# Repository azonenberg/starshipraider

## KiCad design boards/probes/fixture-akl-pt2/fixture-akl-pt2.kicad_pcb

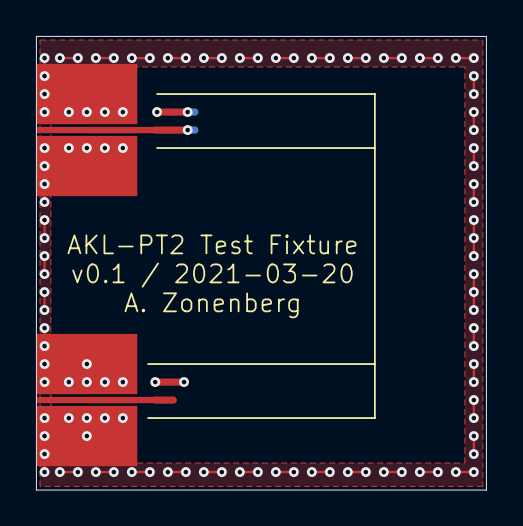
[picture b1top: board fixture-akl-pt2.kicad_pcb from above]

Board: 4 copper layers, 25.0 x 25.2 mm, 3 parts (1 on the bottom side), 2 nets.

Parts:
J1, J2: 901-10511-3; CONN_SMA_EDGE_AMPHENOL_901_10511_3
R1: FC0402E50R0BTT0; EIA_0402_RES_NOSILK_FLIPCHIP

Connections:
/GND: J1.2, J2.2, R1.2
/SIG_TERM: J1.1, R1.1

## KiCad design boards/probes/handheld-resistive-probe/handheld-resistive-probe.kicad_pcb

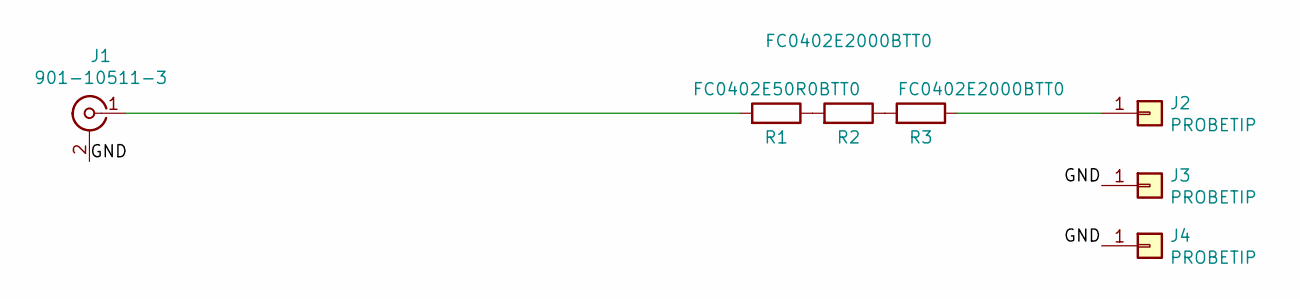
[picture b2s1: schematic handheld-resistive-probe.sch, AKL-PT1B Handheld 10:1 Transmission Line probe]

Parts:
J1: 901-10511-3; CONN_SMA_EDGE_AMPHENOL_901_10511_3
J2, J3, J4: PROBETIP; CONN_MILLMAX_0339_EDGELAUNCH
R1: FC0402E50R0BTT0; EIA_0402_RES_NOSILK_FLIPCHIP
R2, R3: FC0402E2000BTT0; EIA_0402_RES_NOSILK_FLIPCHIP

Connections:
/GND: J1.2 (Ext), J3.1, J4.1
unnamed: J1.1 (In), R1.2
unnamed: J2.1, R3.1
unnamed: R1.1, R2.2
unnamed: R2.1, R3.2

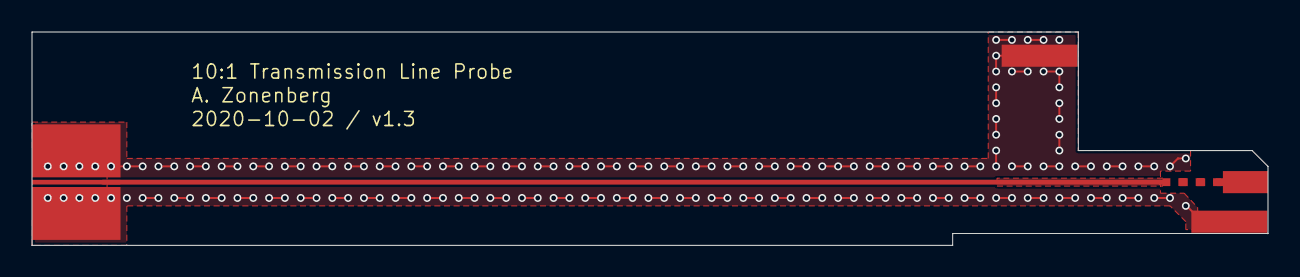
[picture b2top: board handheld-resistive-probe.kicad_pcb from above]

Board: 4 copper layers, 78.2 x 13.5 mm, 7 parts (0 on the bottom side), 5 nets.

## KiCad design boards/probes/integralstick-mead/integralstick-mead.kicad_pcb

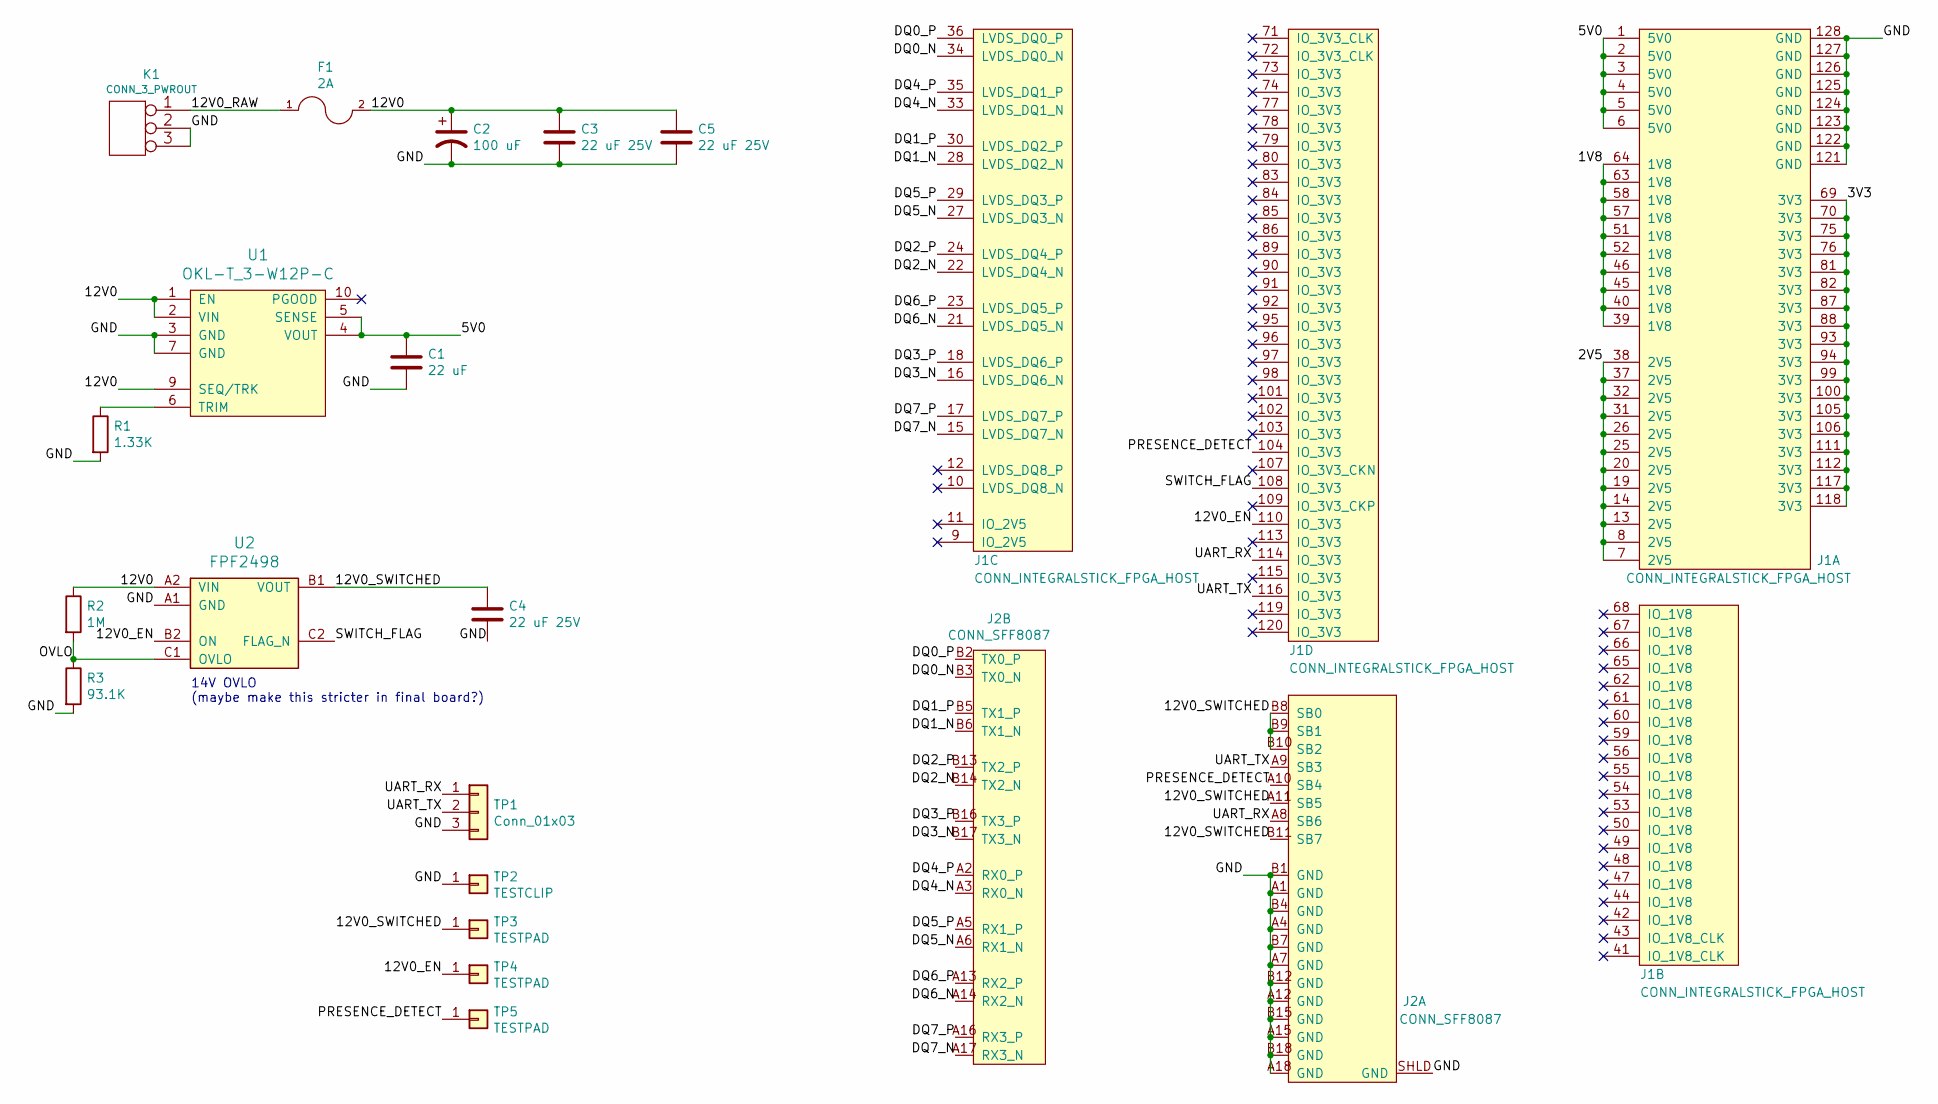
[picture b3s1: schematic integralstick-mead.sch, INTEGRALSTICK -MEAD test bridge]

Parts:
C1: 22 uF; EIA_1210_CAP_NOSILK
C2: 100 uF; CAP_AL_6.3MM_SMT
C3, C4, C5: 22 uF 25V; EIA_1812_CAP_NOSILK
F1: 2A; EIA_0603_RES_NOSILK
J1: CONN_INTEGRALSTICK_FPGA_HOST; CONN_SAMTEC_QSH-060-01-L-D-A
J2: CONN_SFF8087; CONN_SFF8087_MOLEX_75783-0140
K1: CONN_3_PWROUT; CONN_CUI_PJ-058BH_HIPWR_BARREL_NOSLOT
R1: 1.33K; EIA_0402_RES_NOSILK
R2: 1M; EIA_0402_RES_NOSILK
R3: 93.1K; EIA_0402_RES_NOSILK
TP1: Conn_01x03; CONN_HEADER_2.54MM_1x3
TP2: TESTCLIP; TESTPOINT_SMT_KEYSTONE_5016
TP3, TP4, TP5: TESTPAD; TESTPOINT_SMT_0.5MM
U1: OKL-T_3-W12P-C; MODULE_MURATA_OKL-T3-W12
U2: FPF2498; BGA_6_1.3x1.0_0.4MM

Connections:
/1V8: J1.39 (1V8), J1.40 (1V8), J1.45 (1V8), J1.46 (1V8), J1.51 (1V8), J1.52 (1V8), J1.57 (1V8), J1.58 (1V8), J1.63 (1V8), J1.64 (1V8)
/2V5: J1.7 (2V5), J1.8 (2V5), J1.13 (2V5), J1.14 (2V5), J1.19 (2V5), J1.20 (2V5), J1.25 (2V5), J1.26 (2V5), J1.31 (2V5), J1.32 (2V5), J1.37 (2V5), J1.38 (2V5)
/3V3: J1.69 (3V3), J1.70 (3V3), J1.75 (3V3), J1.76 (3V3), J1.81 (3V3), J1.82 (3V3), J1.87 (3V3), J1.88 (3V3), J1.93 (3V3), J1.94 (3V3), J1.99 (3V3), J1.100 (3V3), J1.105 (3V3), J1.106 (3V3), J1.111 (3V3), J1.112 (3V3), J1.117 (3V3), J1.118 (3V3)
/5V0: C1.1, J1.1 (5V0), J1.2 (5V0), J1.3 (5V0), J1.4 (5V0), J1.5 (5V0), J1.6 (5V0), U1.4 (VOUT), U1.5 (SENSE)
/12V0: C2.1, C3.1, C5.1, F1.2, R2.1, U1.1 (EN), U1.2 (VIN), U1.9 (SEQ/TRK), U2.A2 (VIN)
/12V0_EN: J1.110 (IO_3V3), TP4.1, U2.B2 (ON)
/12V0_RAW: F1.1, K1.1
/12V0_SWITCHED: C4.1, J2.A11 (SB5), J2.B8 (SB0), J2.B9 (SB1), J2.B10 (SB2), J2.B11 (SB7), TP3.1, U2.B1 (VOUT)
/DQ0_N: J1.34 (LVDS_DQ0_N), J2.B3 (TX0_N)
/DQ0_P: J1.36 (LVDS_DQ0_P), J2.B2 (TX0_P)
/DQ1_N: J1.28 (LVDS_DQ2_N), J2.B6 (TX1_N)
/DQ1_P: J1.30 (LVDS_DQ2_P), J2.B5 (TX1_P)
/DQ2_N: J1.22 (LVDS_DQ4_N), J2.B14 (TX2_N)
/DQ2_P: J1.24 (LVDS_DQ4_P), J2.B13 (TX2_P)
/DQ3_N: J1.16 (LVDS_DQ6_N), J2.B17 (TX3_N)
/DQ3_P: J1.18 (LVDS_DQ6_P), J2.B16 (TX3_P)
/DQ4_N: J1.33 (LVDS_DQ1_N), J2.A3 (RX0_N)
/DQ4_P: J1.35 (LVDS_DQ1_P), J2.A2 (RX0_P)
/DQ5_N: J1.27 (LVDS_DQ3_N), J2.A6 (RX1_N)
/DQ5_P: J1.29 (LVDS_DQ3_P), J2.A5 (RX1_P)
/DQ6_N: J1.21 (LVDS_DQ5_N), J2.A14 (RX2_N)
/DQ6_P: J1.23 (LVDS_DQ5_P), J2.A13 (RX2_P)
/DQ7_N: J1.15 (LVDS_DQ7_N), J2.A17 (RX3_N)
/DQ7_P: J1.17 (LVDS_DQ7_P), J2.A16 (RX3_P)
/GND: C1.2, C2.2, C3.2, C4.2, C5.2, J1.121 (GND), J1.122 (GND), J1.123 (GND), J1.124 (GND), J1.125 (GND), J1.126 (GND), J1.127 (GND), J1.128 (GND), J2.A1 (GND), J2.A4 (GND), J2.A7 (GND), J2.A12 (GND), J2.A15 (GND), J2.A18 (GND), J2.B1 (GND), J2.B4 (GND), J2.B7 (GND), J2.B12 (GND), J2.B15 (GND), J2.B18 (GND), J2.SHLD (GND), K1.2 (PM), K1.3, R1.2, R3.2, TP1.3, TP2.1, U1.3 (GND), U1.7 (GND), U2.A1 (GND)
/OVLO: R2.2, R3.1, U2.C1 (OVLO)
/PRESENCE_DETECT: J1.104 (IO_3V3), J2.A10 (SB4), TP5.1
/SWITCH_FLAG: J1.108 (IO_3V3), U2.C2 (FLAG_N)
/UART_RX: J1.114 (IO_3V3), J2.A8 (SB6), TP1.1
/UART_TX: J1.116 (IO_3V3), J2.A9 (SB3), TP1.2
unnamed: R1.1, U1.6 (TRIM)

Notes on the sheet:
14V OVLO (maybe make this stricter in final board?)

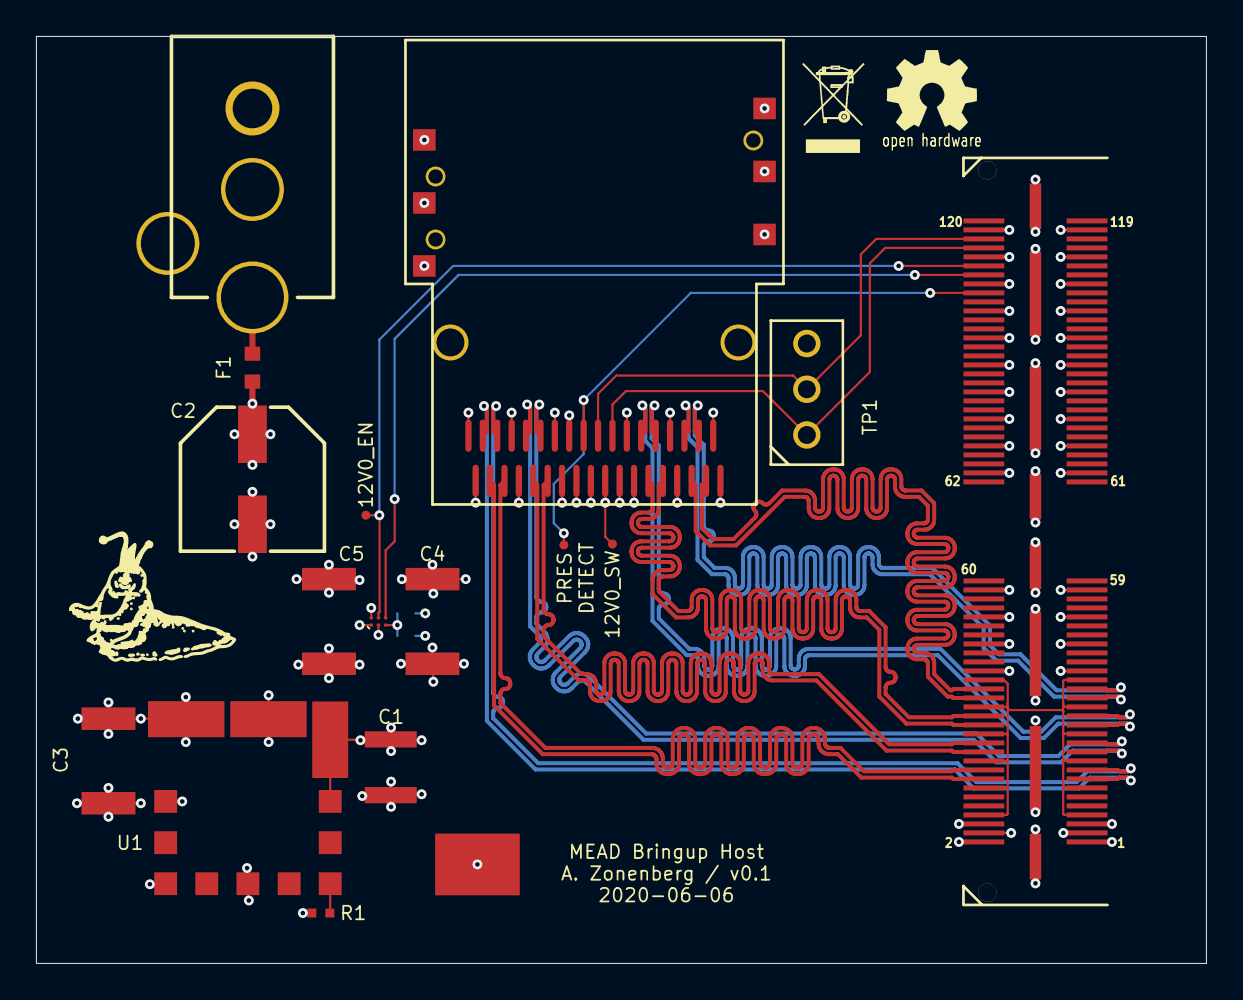
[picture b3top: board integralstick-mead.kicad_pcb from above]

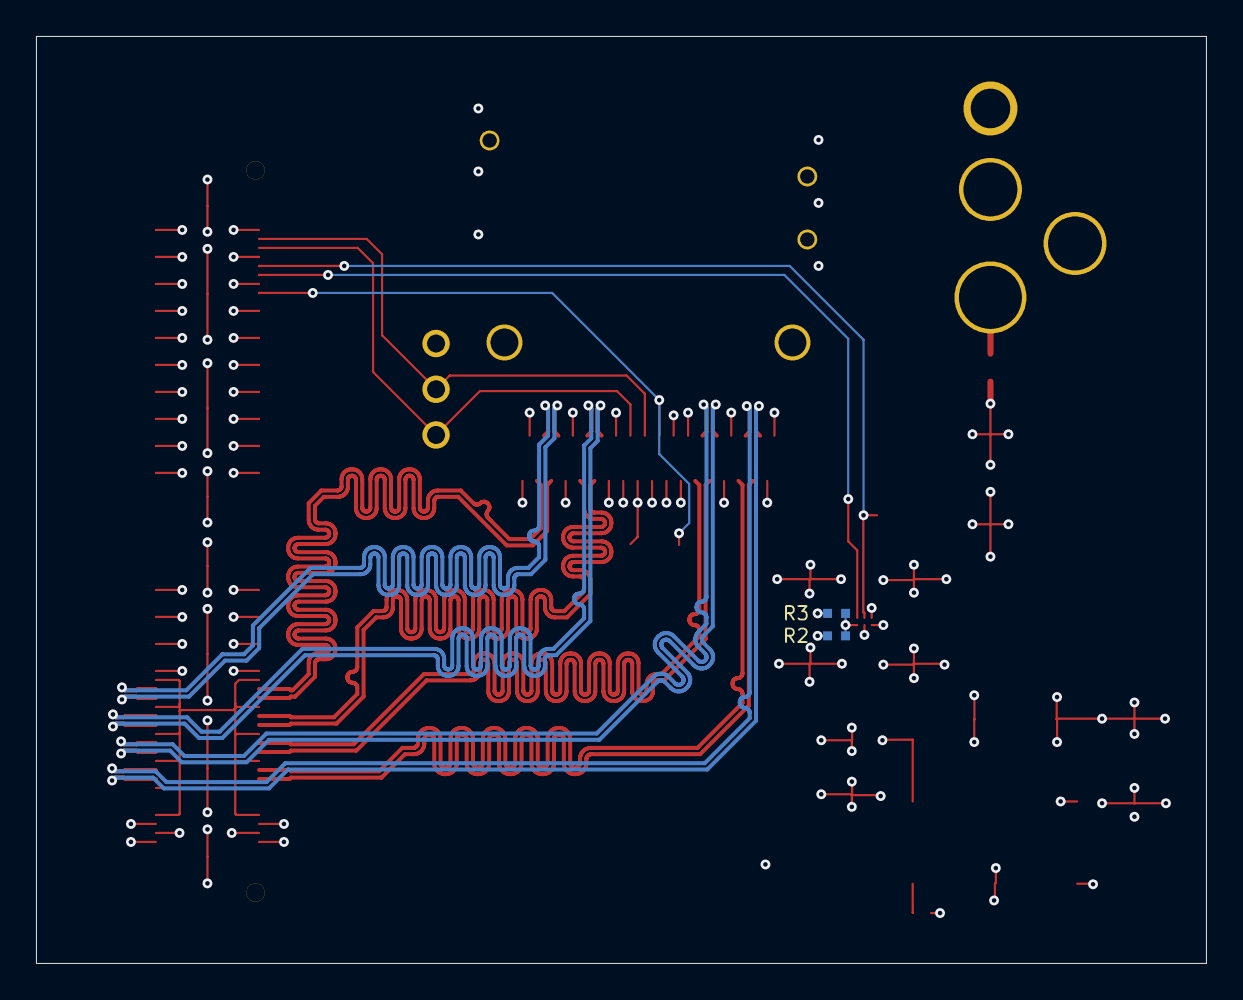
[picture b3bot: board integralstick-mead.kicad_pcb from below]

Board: 4 copper layers, 65.0 x 51.5 mm, 19 parts (2 on the bottom side), 31 nets.

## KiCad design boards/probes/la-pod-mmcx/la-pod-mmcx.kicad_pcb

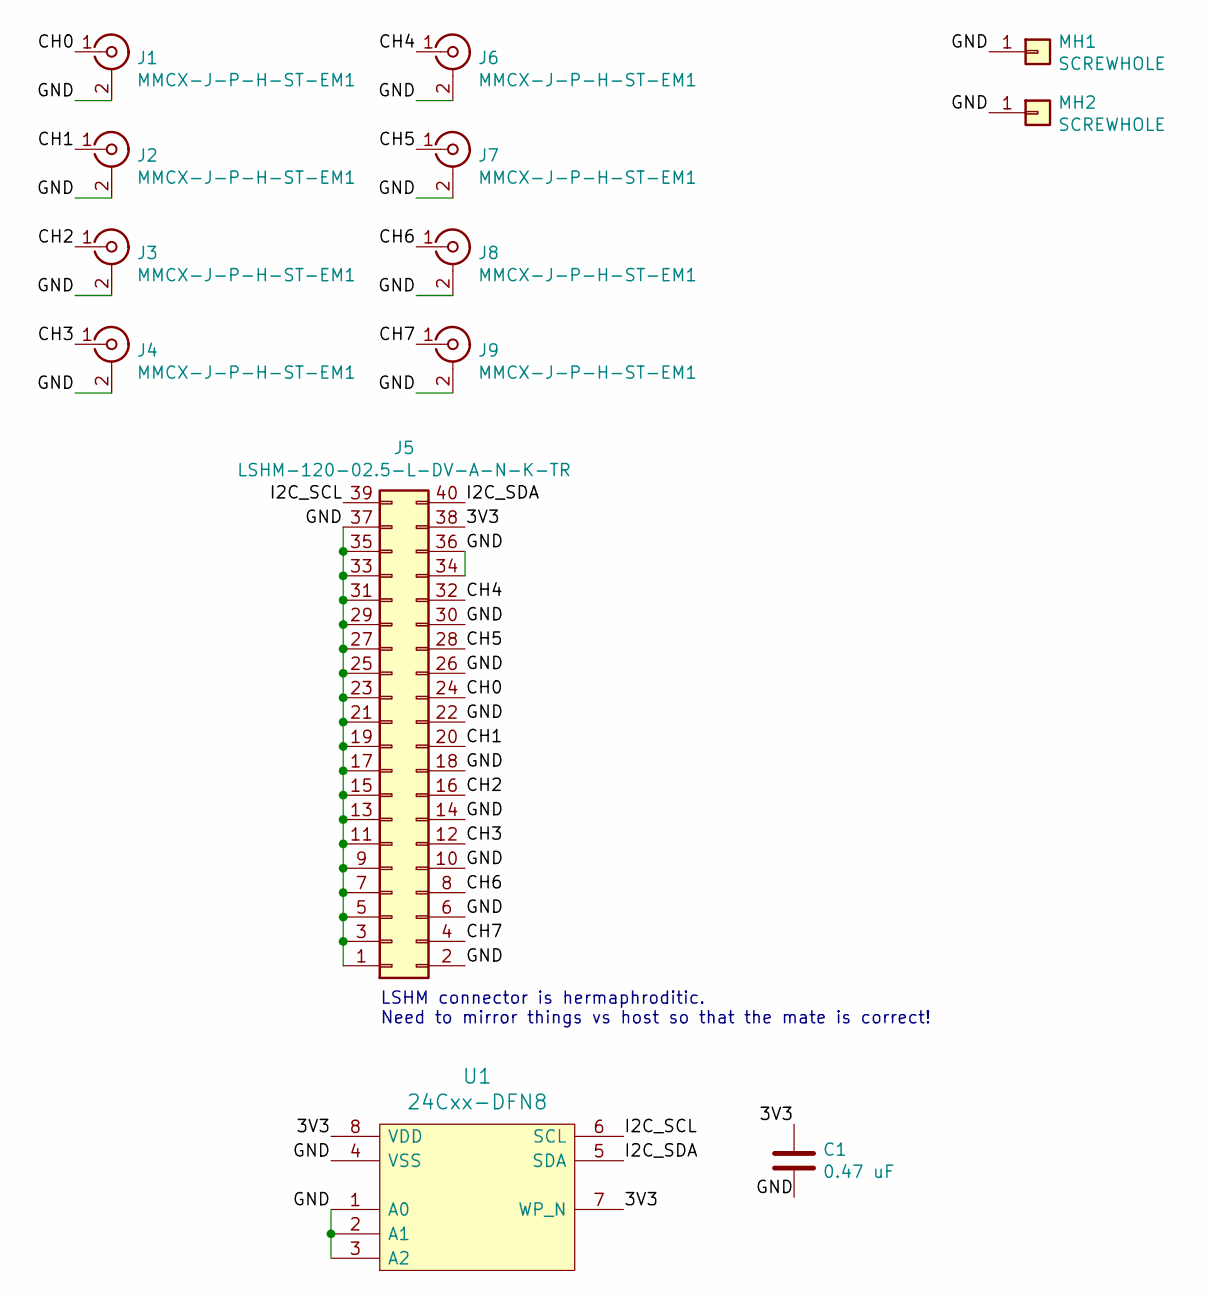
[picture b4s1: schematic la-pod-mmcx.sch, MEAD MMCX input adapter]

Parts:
C1: 0.47 uF; EIA_0402_CAP_NOSILK
J1, J2, J3, J4, J6, J7, J8, J9: MMCX-J-P-H-ST-EM1; CONN_MMCX_J_P_H_ST_EM1_0P7MM_CENTER
J5: LSHM-120-02.5-L-DV-A-N-K-TR; CONN_SAMTEC_LSHM-120-02.5-L-DV-A-N-K-TR
MH1, MH2: SCREWHOLE; MECHANICAL_CLEARANCEHOLE_4_40
U1: 24Cxx-DFN8; DFN_8_0.5MM_3x3MM

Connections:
/3V3: C1.1, J5.38, U1.7 (WP_N), U1.8 (VDD)
/CH0: J1.1 (In), J5.24
/CH1: J2.1 (In), J5.20
/CH2: J3.1 (In), J5.16
/CH3: J4.1 (In), J5.12
/CH4: J5.32, J6.1 (In)
/CH5: J5.28, J7.1 (In)
/CH6: J5.8, J8.1 (In)
/CH7: J5.4, J9.1 (In)
/GND: C1.2, J1.2 (Ext), J2.2 (Ext), J3.2 (Ext), J4.2 (Ext), J5.1, J5.2, J5.3, J5.5, J5.6, J5.7, J5.9, J5.10, J5.11, J5.13, J5.14, J5.15, J5.17, J5.18, J5.19, J5.21, J5.22, J5.23, J5.25, J5.26, J5.27, J5.29, J5.30, J5.31, J5.33, J5.34, J5.35, J5.36, J5.37, J6.2 (Ext), J7.2 (Ext), J8.2 (Ext), J9.2 (Ext), MH1.1, MH2.1, U1.1 (A0), U1.2 (A1), U1.3 (A2), U1.4 (VSS)
/I2C_SCL: J5.39, U1.6 (SCL)
/I2C_SDA: J5.40, U1.5 (SDA)

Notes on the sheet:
LSHM connector is hermaphroditic. Need to mirror things vs host so that the mate is correct!

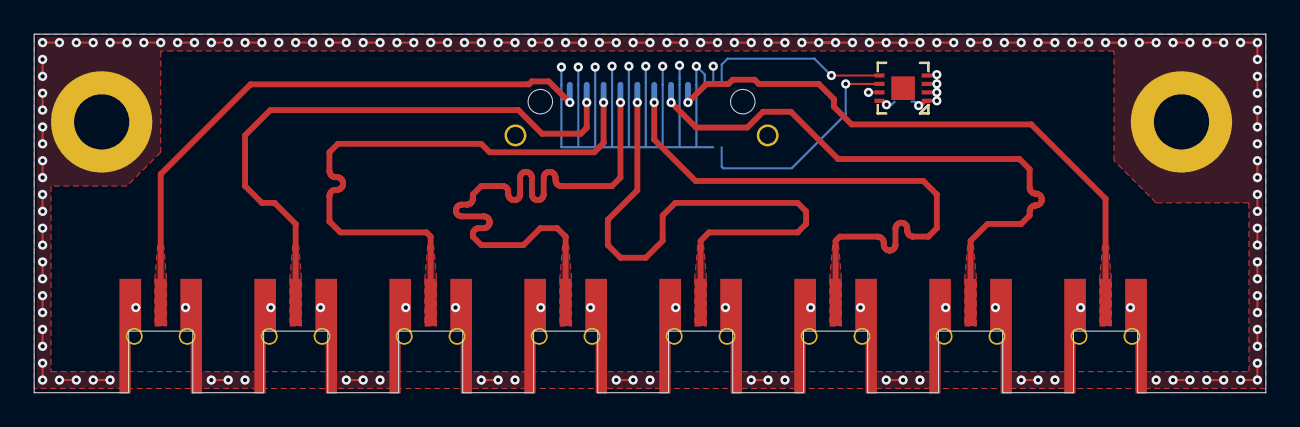
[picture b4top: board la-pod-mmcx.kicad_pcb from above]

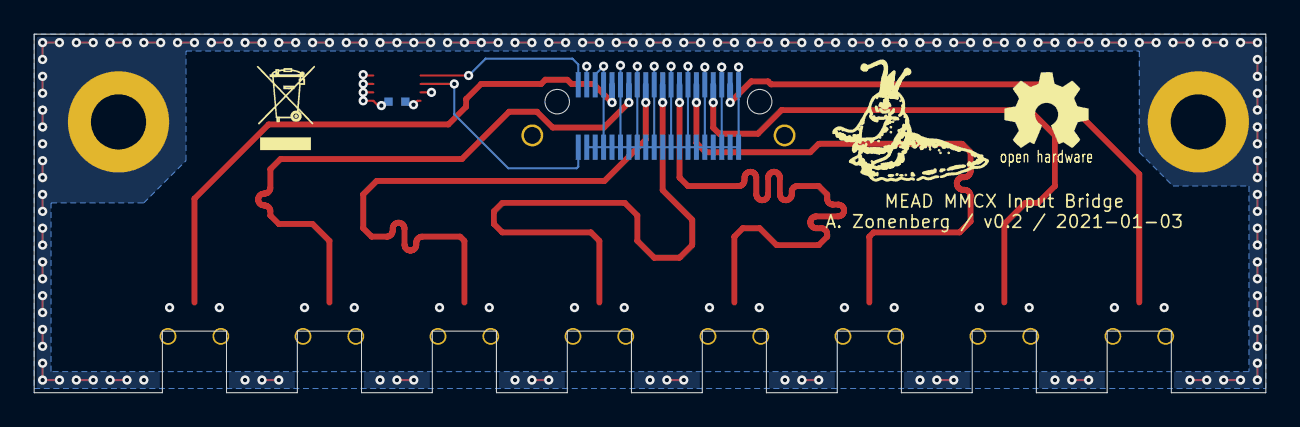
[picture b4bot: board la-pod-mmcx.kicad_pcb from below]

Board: 4 copper layers, 73.0 x 21.2 mm, 13 parts (2 on the bottom side), 12 nets.

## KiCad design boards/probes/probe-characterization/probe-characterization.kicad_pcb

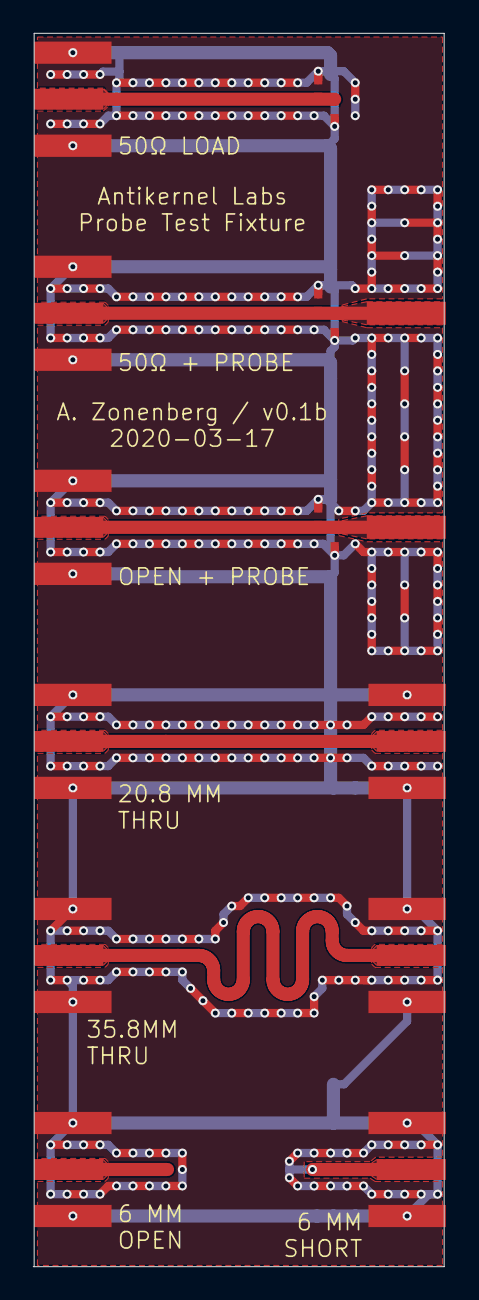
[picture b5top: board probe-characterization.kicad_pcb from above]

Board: 2 copper layers, 24.9 x 74.9 mm, 17 parts (0 on the bottom side), 6 nets.

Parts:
J1, J2, J3, J4, J5, J6, J7, J8, J9: SMA; CONN_SMA_EDGE_SAMTEC_SMA_J_P_H_ST_EM1
J10, J11: PROBE; CONN_MILLMAX_0339_EDGELAUNCH
R1, R2, R4, R5: 100; EIA_0402_RES_NOSILK_FLIPCHIP
R3, R6: DNP; EIA_0402_RES_NOSILK_FLIPCHIP

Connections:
/GND: J1.2, J2.2, J3.2, J4.2, J5.2, J6.2, J7.1, J7.2, J8.2, J9.2, R1.2, R2.2, R3.2, R4.2, R5.2, R6.2
unnamed: J1.1, R1.1, R4.1
unnamed: J4.1, J8.1
unnamed: J5.1, J9.1
unnamed: J2.1, J10.1, R2.1, R5.1
unnamed: J3.1, J11.1, R3.1, R6.1
